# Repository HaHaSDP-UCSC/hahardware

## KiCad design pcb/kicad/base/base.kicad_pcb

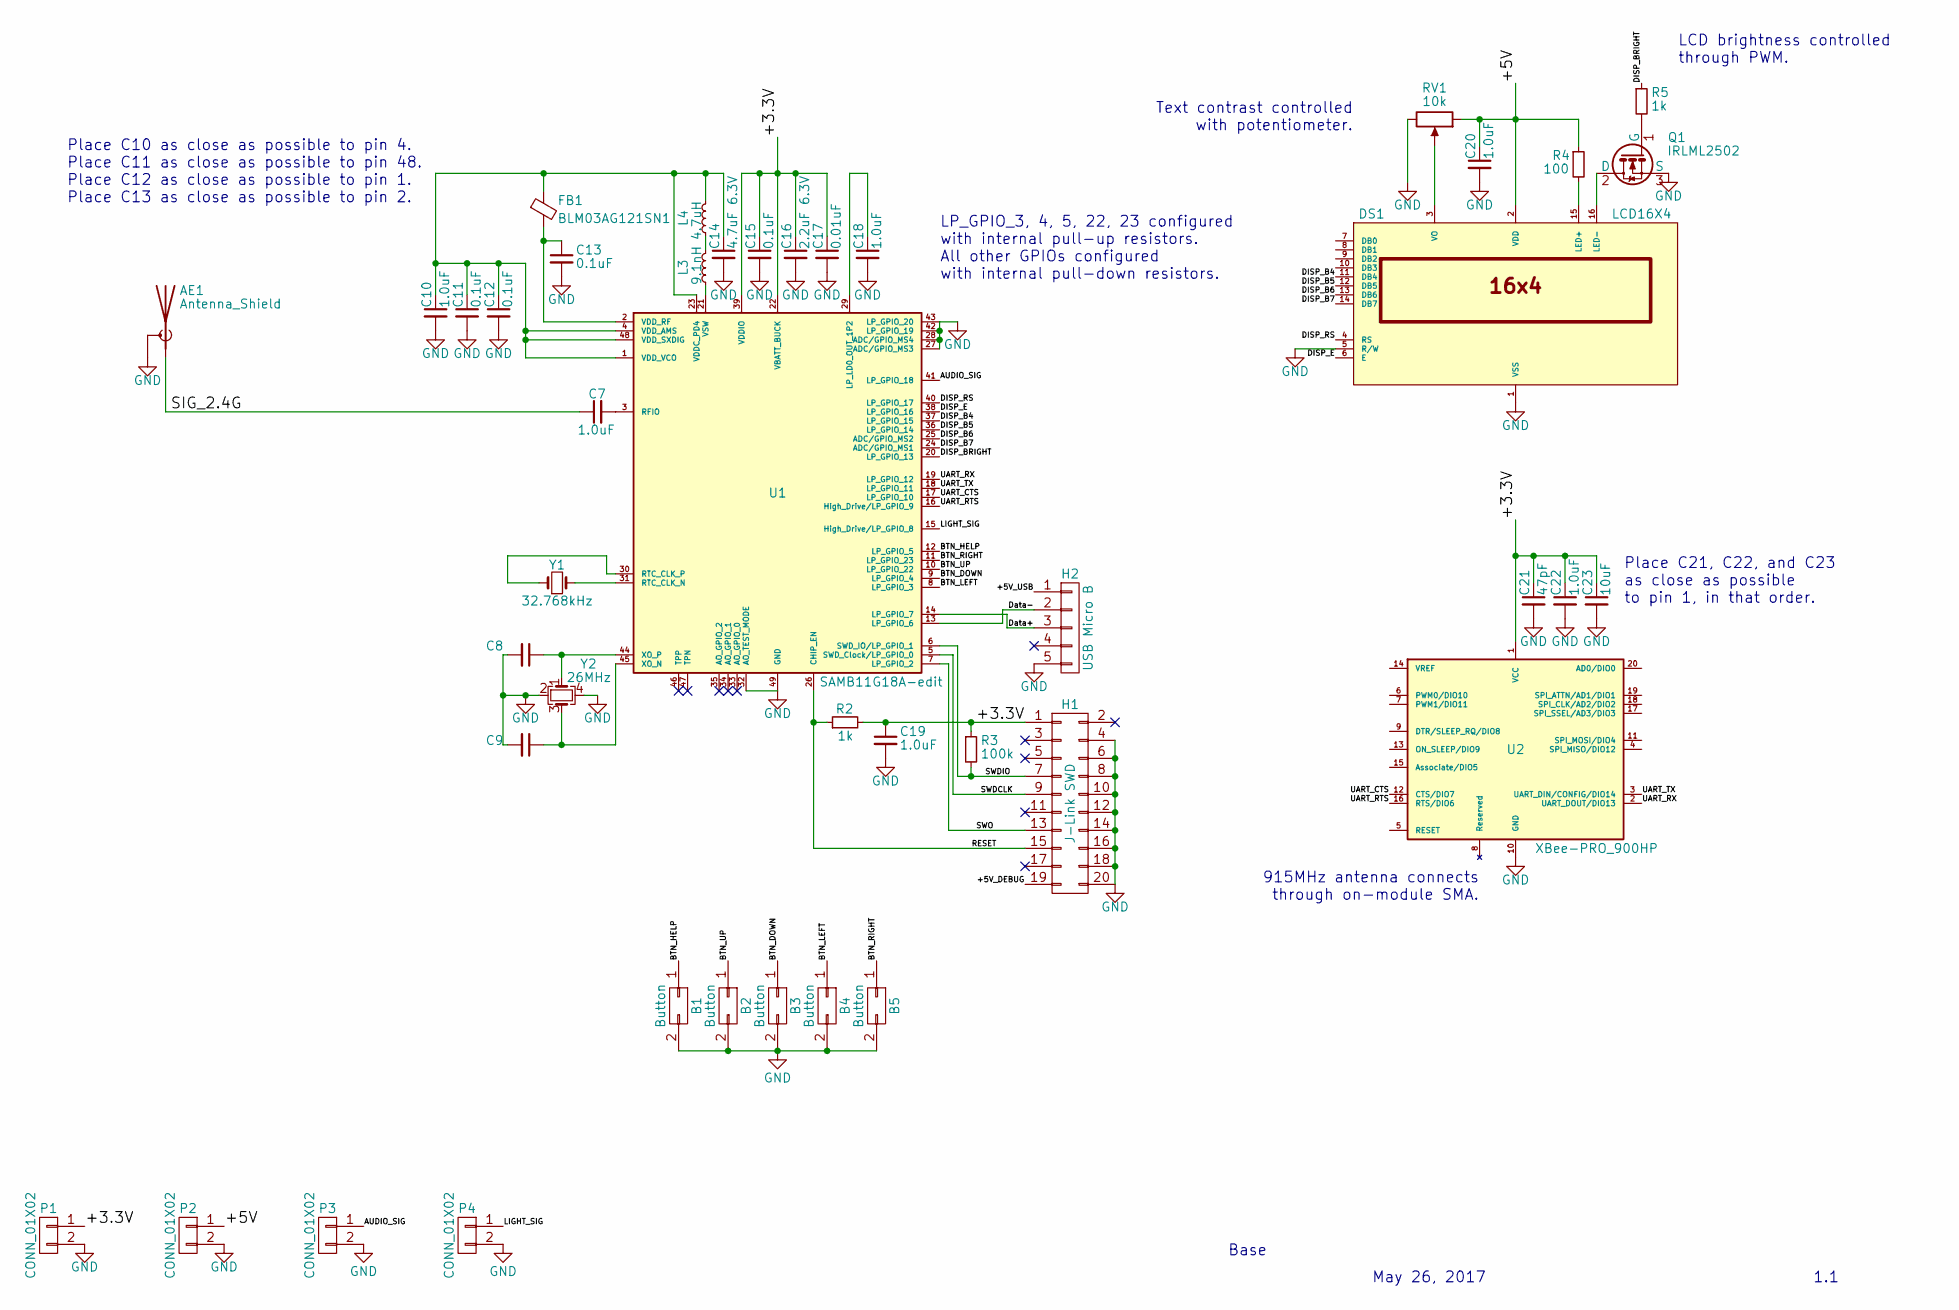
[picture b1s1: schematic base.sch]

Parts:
AE1: Antenna_Shield; Patch_Antenna_2.4GHz
B1, B2, B3, B4, B5: Button; E-Switch_KS01Q01
C7, C10, C18, C19, C20, C22: 1.0uF; C_0402
C8, C9: C_Small; C_0402
C11, C12, C13, C15: 0.1uF; C_0402
C14: 4.7uF 6.3V; C_0402
C16: 2.2uF 6.3V; C_0402
C17: 0.01uF; C_0402
C21: 47pF; C_0402
C23: 10uF; C_0402
DS1: LCD16X4; CFAH1604A
FB1: BLM03AG121SN1; C_0603_HandSoldering
H1: J-Link SWD; Socket_Strip_Straight_2x10_Pitch2.54mm_Drill0.889mm
H2: USB Micro B; USB_Micro-B_10118194-000XLF
L3: 9.1nH; C_0402
L4: 4.7uH; C_0805_HandSoldering
P1, P2, P3, P4: CONN_01X02; OSTTEXX0164_2pin_3.5mm
Q1: IRLML2502; SOT-23
R2, R5: 1k; C_0402
R3: 100k; C_0402
R4: 100; C_0402
RV1: 10k; Potentiometer_Trimmer_Bourns_3309W
U1: SAMB11G18A-edit; QFN-48-1EP_6x6mm_Pitch0.4mm
U2: XBee-PRO_900HP; Digi_XBee-PRO_TH
Y1: 32.768kHz; Crystal_SMD_3215-2pin_3.2x1.5mm
Y2: 26MHz; Crystal_SMD_3225-4pin_3.2x2.5mm

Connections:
/+3.3V: C15.1, C16.1, C17.1, C19.1, C21.1, C22.1, C23.1, H1.1, P1.1, R2.2, R3.1, U1.22 (VBATT_BUCK), U1.39 (VDDIO), U2.1 (VCC)
/+5V: C20.1, DS1.2 (VDD), P2.1, R4.1, RV1.1
/+5V_DEBUG: H1.19
/+5V_USB: H2.1
/AUDIO_SIG: P3.1, U1.41 (LP_GPIO_18)
/BTN_DOWN: B3.1, U1.9 (LP_GPIO_4)
/BTN_HELP: B1.1, U1.12 (LP_GPIO_5)
/BTN_LEFT: B4.1, U1.8 (LP_GPIO_3)
/BTN_RIGHT: B5.1, U1.11 (LP_GPIO_23)
/BTN_UP: B2.1, U1.10 (LP_GPIO_22)
/DISP_B4: DS1.11 (DB4), U1.37 (LP_GPIO_15)
/DISP_B5: DS1.12 (DB5), U1.36 (LP_GPIO_14)
/DISP_B6: DS1.13 (DB6), U1.25 (ADC/GPIO_MS2)
/DISP_B7: DS1.14 (DB7), U1.24 (ADC/GPIO_MS1)
/DISP_BRIGHT: R5.1, U1.20 (LP_GPIO_13)
/DISP_E: DS1.6 (E), U1.38 (LP_GPIO_16)
/DISP_RS: DS1.4 (RS), U1.40 (LP_GPIO_17)
/Data+: H2.3, U1.14 (LP_GPIO_7)
/Data-: H2.2, U1.13 (LP_GPIO_6)
/LIGHT_SIG: P4.1, U1.15 (High_Drive/LP_GPIO_8)
/RESET: H1.15, R2.1, U1.26 (CHIP_EN)
/SIG_2.4G: AE1.1 (A), C7.1
/SWDCLK: H1.9, U1.5 (SWD_Clock/LP_GPIO_0)
/SWDIO: H1.7, R3.2, U1.6 (SWD_IO/LP_GPIO_1)
/SWO: H1.13, U1.7 (LP_GPIO_2)
/UART_CTS: U1.17 (LP_GPIO_10), U2.12 (CTS/DIO7)
/UART_RTS: U1.16 (High_Drive/LP_GPIO_9), U2.16 (RTS/DIO6)
/UART_RX: U1.19 (LP_GPIO_12), U2.2 (UART_DOUT/DIO13)
/UART_TX: U1.18 (LP_GPIO_11), U2.3 (UART_DIN/CONFIG/DIO14)
GND: AE1.2 (Shield), B1.2, B2.2, B3.2, B4.2, B5.2, C8.2, C9.2, C10.2, C11.2, C12.2, C13.2, C14.2, C15.2, C16.2, C17.2, C18.2, C19.2, C20.2, C21.2, C22.2, C23.2, DS1.1 (VSS), DS1.5 (R/W), H1.4, H1.6, H1.8, H1.10, H1.12, H1.14, H1.16, H1.18, H1.20, H2.5, P1.2, P2.2, P3.2, P4.2, Q1.3 (S), RV1.3, U1.27 (ADC/GPIO_MS3), U1.28 (ADC/GPIO_MS4), U1.32 (AO_TEST_MODE), U1.42 (LP_GPIO_19), U1.43 (LP_GPIO_20), U1.49 (GND), U2.10 (GND), Y2.2, Y2.4
unnamed: C7.2, U1.3 (RFIO)
unnamed: C8.1, U1.44 (XO_P), Y2.1
unnamed: C9.1, U1.45 (XO_N), Y2.3
unnamed: C10.1, C11.1, C12.1, C14.1, FB1.1, L4.2, U1.1 (VDD_VCO), U1.4 (VDD_AMS), U1.23 (VDDC_PD4), U1.48 (VDD_SXDIG)
unnamed: C13.1, FB1.2, U1.2 (VDD_RF)
unnamed: C18.1, U1.29 (LP_LD0_OUT_1P2)
unnamed: DS1.3 (VO), RV1.2
unnamed: DS1.15 (LED+), R4.2
unnamed: DS1.16 (LED-), Q1.2 (D)
unnamed: L3.1, U1.21 (VSW)
unnamed: L3.2, L4.1
unnamed: Q1.1 (G), R5.2
unnamed: U1.30 (RTC_CLK_P), Y1.1
unnamed: U1.31 (RTC_CLK_N), Y1.2

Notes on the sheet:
Base
Place C10 as close as possible to pin 4. Place C11 as close as possible to pin 48. Place C12 as close as possible to pin 1. Place C13 as close as possible to pin 2.
LP_GPIO_3, 4, 5, 22, 23 configured with internal pull-up resistors. All other GPIOs configured with internal pull-down resistors.
Place C21, C22, and C23 as close as possible to pin 1, in that order.
915MHz antenna connects through on-module SMA.
May 26, 2017
1.1
Text contrast controlled with potentiometer.
LCD brightness controlled through PWM.

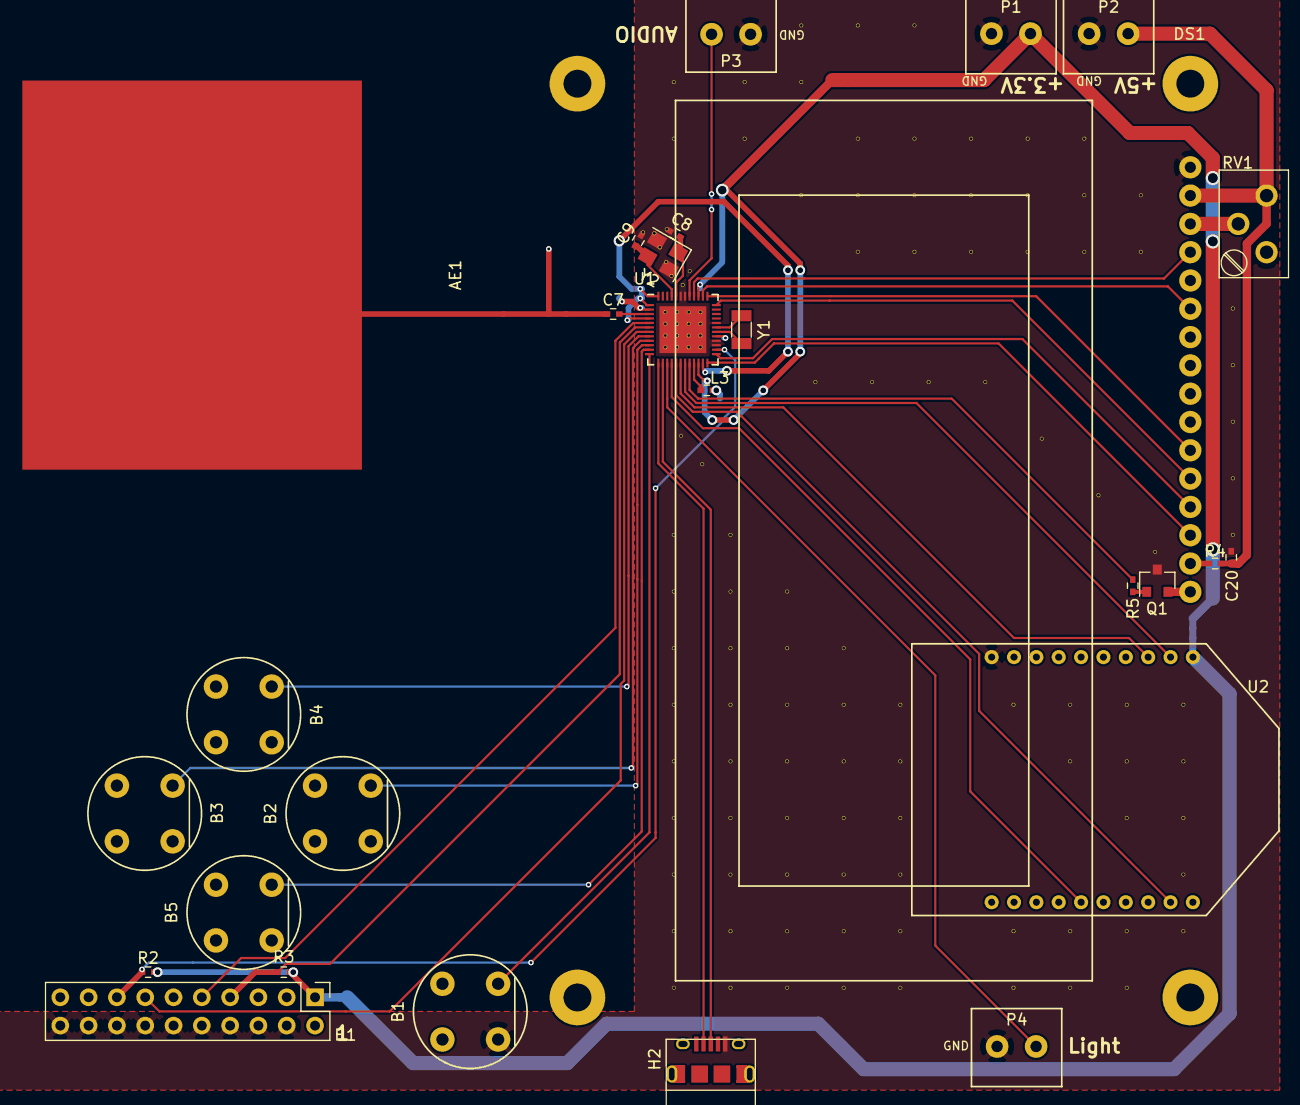
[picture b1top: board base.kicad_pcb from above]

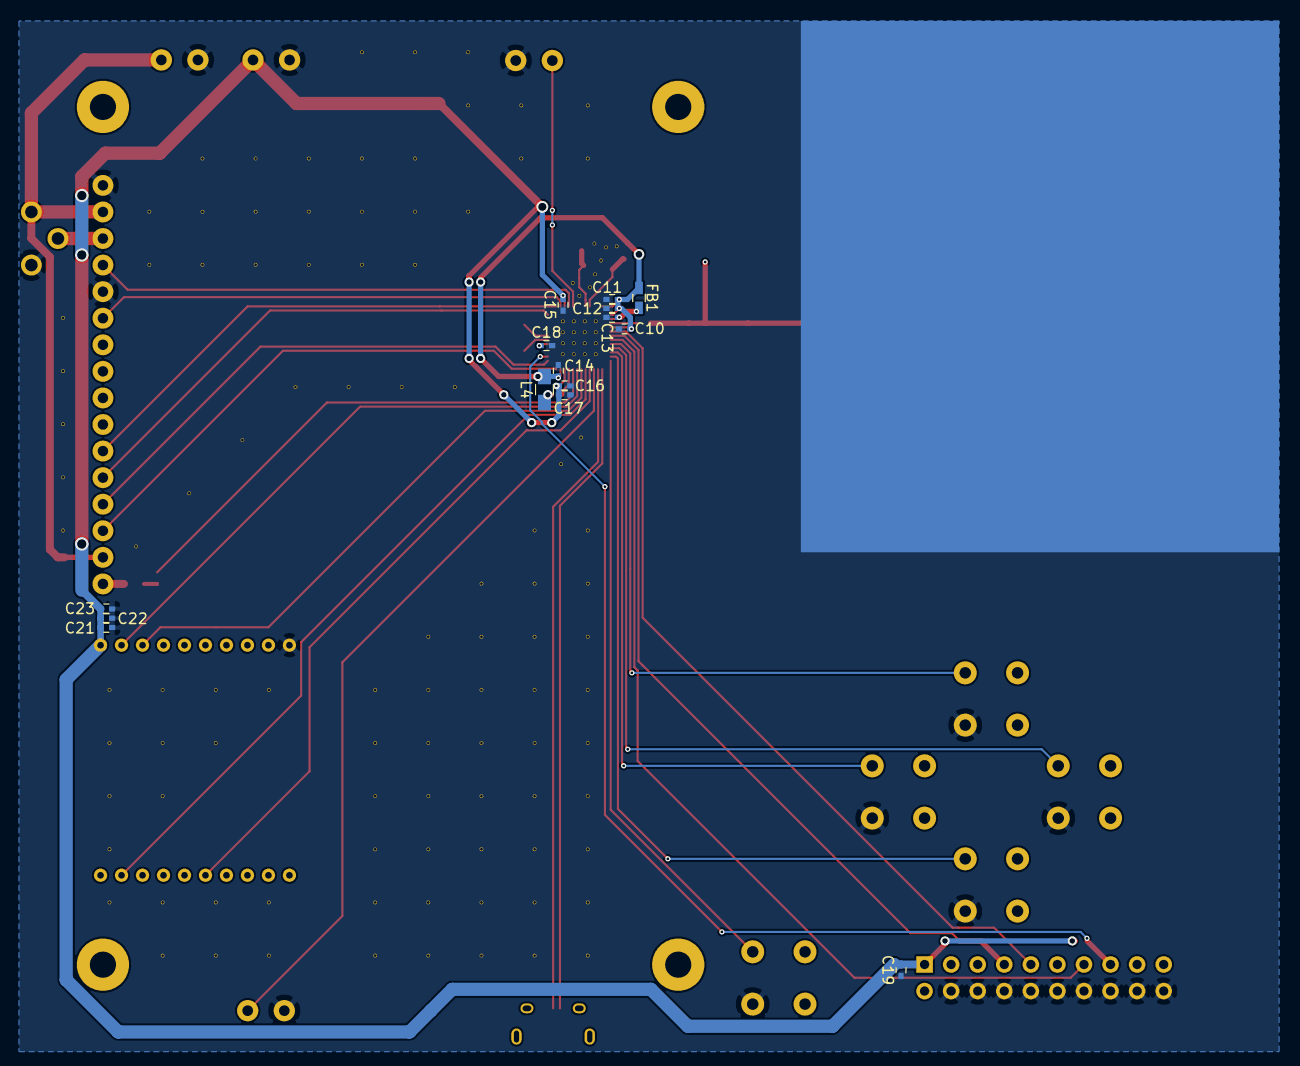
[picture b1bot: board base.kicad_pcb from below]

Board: 2 copper layers, 43 parts (15 on the bottom side), 42 nets.

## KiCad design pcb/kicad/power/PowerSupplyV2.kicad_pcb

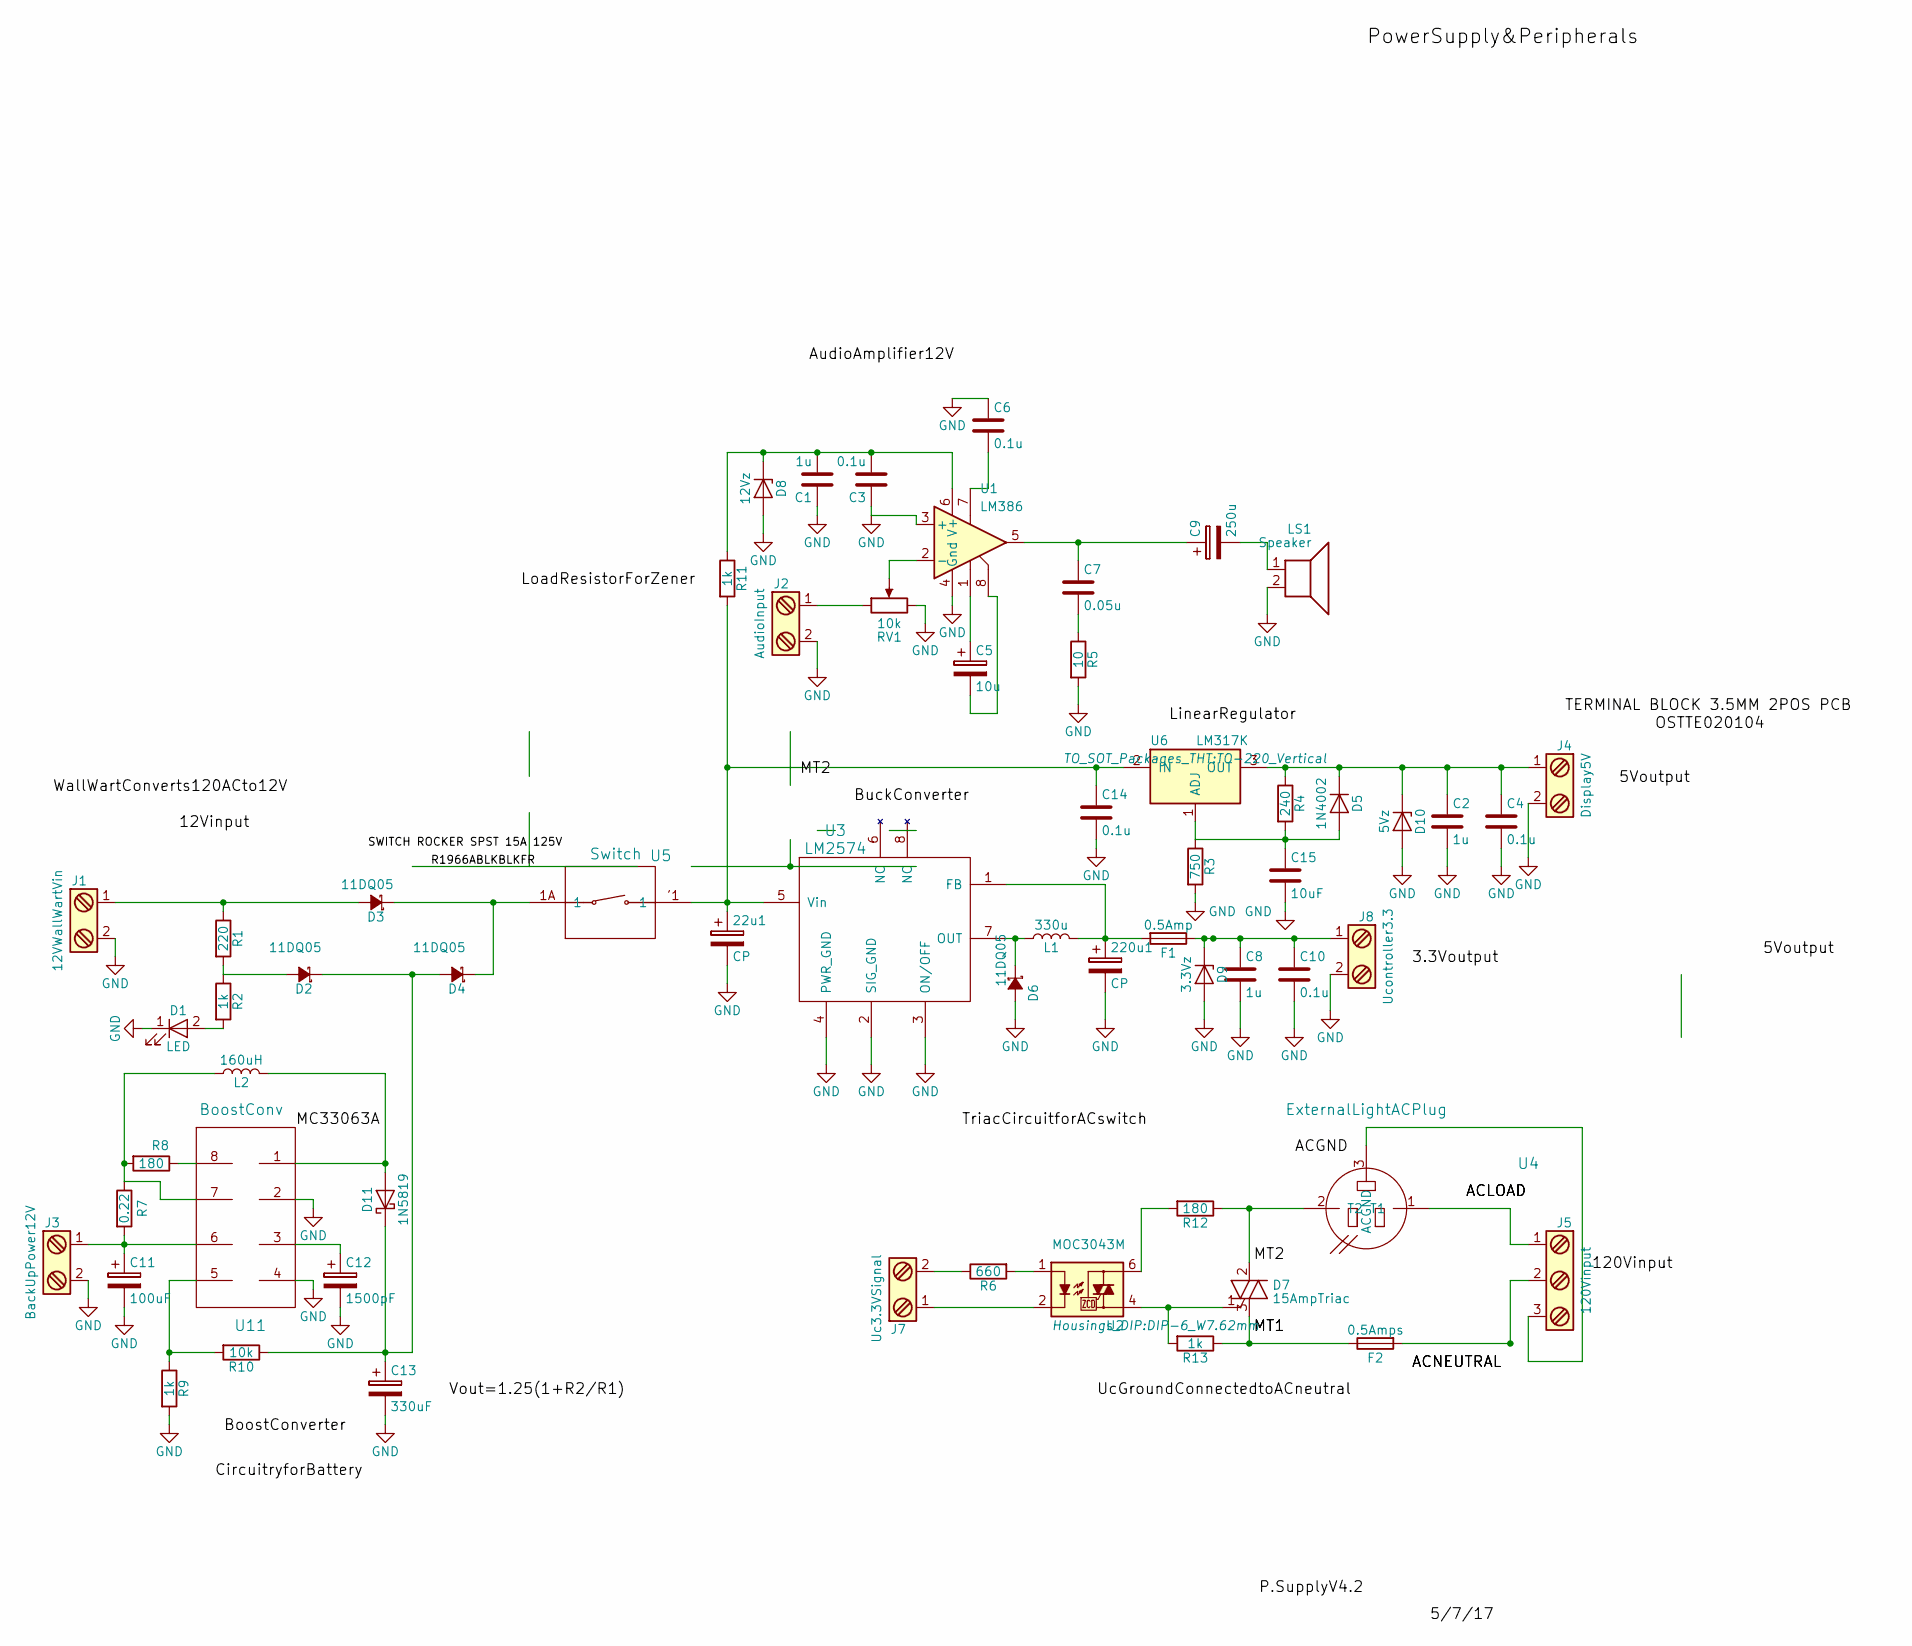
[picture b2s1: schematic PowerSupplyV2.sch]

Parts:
22u1, 220u1: CP; CP_Radial_D6.3mm_P2.50mm
C1, C2, C8: 1u; R_Axial_DIN0204_L3.6mm_D1.6mm_P7.62mm_Horizontal
C3, C4, C6, C10, C14: 0.1u; R_Axial_DIN0204_L3.6mm_D1.6mm_P7.62mm_Horizontal
C5: 10u; CP_Radial_D6.3mm_P2.50mm
C7: 0.05u; C_0805_HandSoldering
C9: 250u; CP_Radial_D6.3mm_P2.50mm
C11: 100uF; CP_Radial_D6.3mm_P2.50mm
C12: 1500pF; CP_Radial_D6.3mm_P2.50mm
C13: 330uF; CP_Radial_D6.3mm_P2.50mm
C15: 10uF; R_Axial_DIN0204_L3.6mm_D1.6mm_P7.62mm_Horizontal
D1: LED; LED_D5.0mm_Horizontal_O1.27mm_Z3.0mm
D2, D3, D4, D6: 11DQ05; D_DO-15_P5.08mm_Vertical_KathodeUp
D5: 1N4002; D_DO-15_P5.08mm_Vertical_KathodeUp
D7: 15AmpTriac; TO-220_Vertical
D8: 12Vz; D_SOD-323_HandSoldering
D9: 3.3Vz; D_SOD-323_HandSoldering
D10: 5Vz; D_SOT-23_ANK
D11: 1N5819; D_DO-15_P5.08mm_Vertical_KathodeUp
F1: 0.5Amp; FuseTH500mA
F2: 0.5Amps; FuseTH500mA
J1: 12VWallWartVin; BARREL_JACK
J2: AudioInput; BlockTerminal3.5mm
J3: BackUpPower12V; NIMH4.8V
J4: Display5V; BlockTerminal3.5mm
J5: 120Vinput; 703w0053
J7: Uc3.3VSignal; BlockTerminal3.5mm
J8: Ucontroller3.3; BlockTerminal3.5mm
L1: 330u; Choke_SMD_12x12mm_h4.5mm
L2: 160uH; Choke_SMD_12x12mm_h4.5mm
LS1: Speaker; BlockTerminal3.5mm
R1: 220; R_Axial_DIN0309_L9.0mm_D3.2mm_P2.54mm_Vertical
R2, R9, R11, R13: 1k; R_Axial_DIN0309_L9.0mm_D3.2mm_P2.54mm_Vertical
R3: 750; R_Axial_DIN0309_L9.0mm_D3.2mm_P2.54mm_Vertical
R4: 240; R_Axial_DIN0309_L9.0mm_D3.2mm_P2.54mm_Vertical
R5: 10; R_0805_HandSoldering
R6: 660; R_Axial_DIN0309_L9.0mm_D3.2mm_P2.54mm_Vertical
R7: 0.22; R_Axial_DIN0309_L9.0mm_D3.2mm_P2.54mm_Vertical
R8, R12: 180; R_Axial_DIN0309_L9.0mm_D3.2mm_P2.54mm_Vertical
R10: 10k; R_Axial_DIN0309_L9.0mm_D3.2mm_P2.54mm_Vertical
RV1: 10k; Potentiometer_Alps_RK09K_Vertical
U1: LM386; DIP-8_W7.62mm
U2: MOC3043M; DIP-6_W7.62mm
U3: LM2574; PDIP-8
U4: ExternalLightACPlug; 739W-X203
U5: Switch
U6: LM317K; TO-220_Vertical
U11: BoostConv; DIP-8_W7.62mm

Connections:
GND: 22u1.2, 220u1.2, C1.1, C2.2, C3.1, C4.2, C6.1, C8.2, C10.2, C11.2, C12.2, C13.2, C14.2, C15.2, D1.1 (K), D6.2 (A), D8.2 (A), D9.2 (A), D10.2 (A), J1.2, J2.2, J3.2, J4.2, J8.2, LS1.2, R3.2, R5.2, R9.2, RV1.3, U1.3 (+), U1.4 (Gnd), U3.2 (SIG_GND), U3.3 (ON/OFF), U3.4 (PWR_GND), U11.2, U11.4
unnamed: 22u1.1, C14.1, R11.2, U3.5 (Vin), U5.'1, U6.2 (IN)
unnamed: 220u1.1, F1.2, L1.2, U3.1 (FB)
unnamed: C1.2, C3.2, D8.1 (K), R11.1, U1.6 (V+)
unnamed: C2.1, C4.1, D5.1 (K), D10.1 (K), J4.1, R4.1, U6.3 (OUT)
unnamed: C5.1, U1.1
unnamed: C5.2, U1.8
unnamed: C6.2, U1.7
unnamed: C7.1, C9.1, U1.5
unnamed: C7.2, R5.1
unnamed: C9.2, LS1.1
unnamed: C8.1, C10.1, D9.1 (K), F1.1, J8.1
unnamed: C11.1, J3.1, R7.2, U11.6
unnamed: C12.1, U11.3
unnamed: C13.1, D2.1 (K), D4.2 (A), D11.1 (K), R10.1
unnamed: C15.1, D5.2 (A), R3.1, R4.2, U6.1 (ADJ)
unnamed: D1.2 (A), R2.2
unnamed: D2.2 (A), R1.2, R2.1
unnamed: D3.1 (K), D4.1 (K), U5.1A
unnamed: D3.2 (A), J1.1, R1.1
unnamed: D6.1 (K), L1.1, U3.7 (OUT)
unnamed: D7.1 (G), R13.2, U2.4
unnamed: D7.2 (A1), R12.1, U4.2 (T2)
unnamed: D7.3 (A2), F2.1, R13.1
unnamed: D11.2 (A), L2.2, U11.1
unnamed: F2.2, J5.2
unnamed: J2.1, RV1.1
unnamed: J5.1, U4.1 (T1)
unnamed: J5.3, U4.3 (ACGND)
unnamed: J7.1, U2.2
unnamed: J7.2, R6.1
unnamed: L2.1, R7.1, R8.2, U11.7
unnamed: R6.2, U2.1
unnamed: R8.1, U11.8
unnamed: R9.1, R10.2, U11.5
unnamed: R12.2, U2.6
unnamed: RV1.2, U1.2 (-)

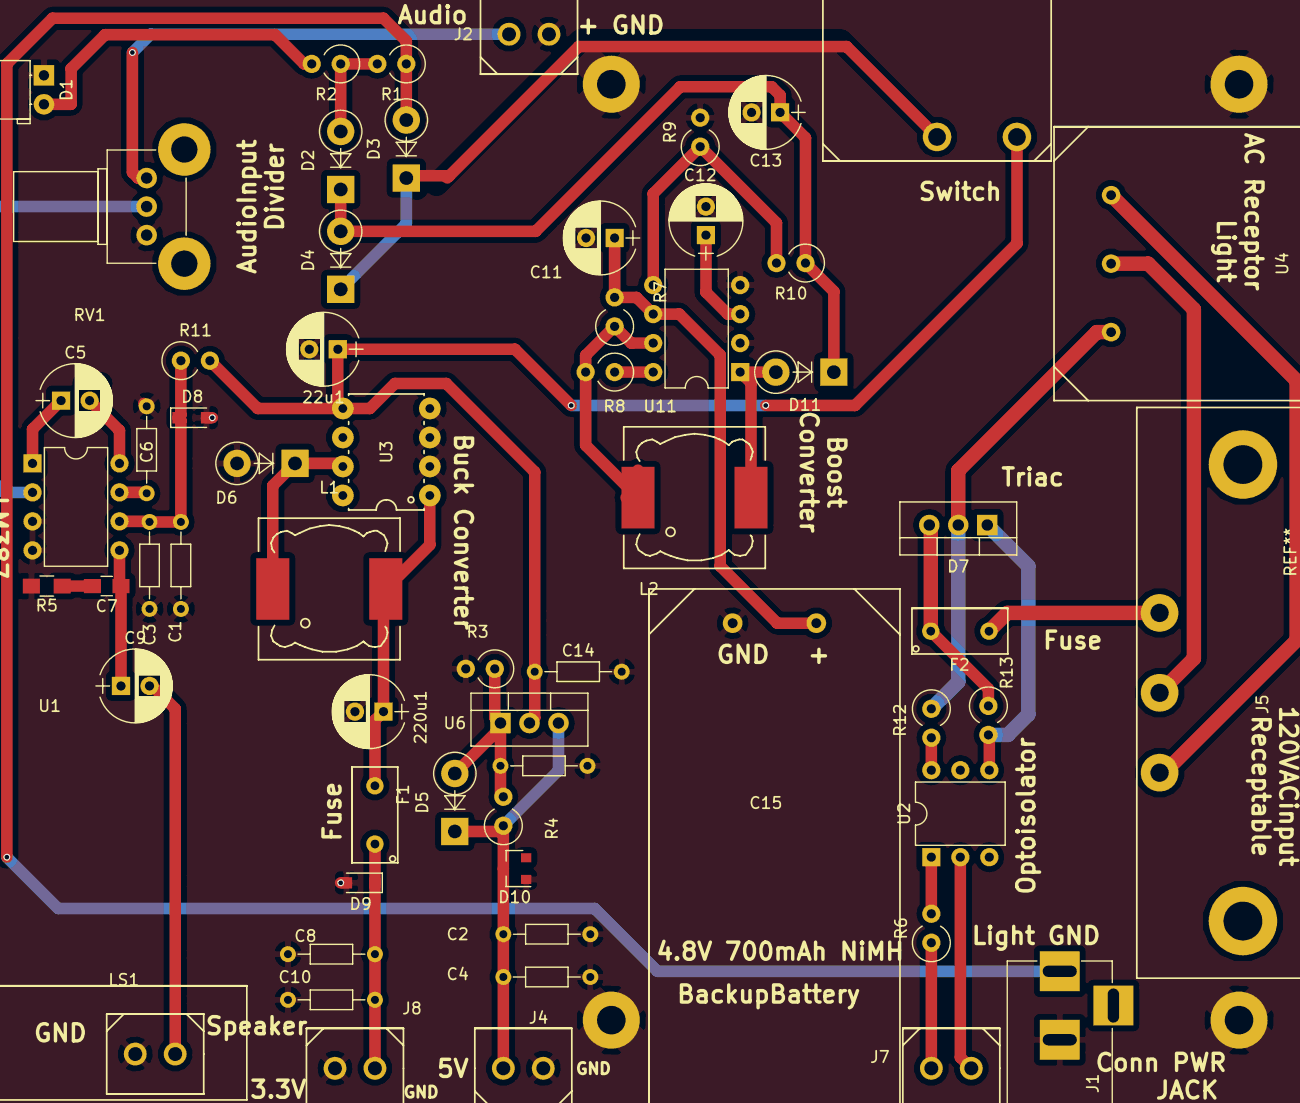
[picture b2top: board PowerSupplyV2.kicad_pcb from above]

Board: 2 copper layers, 61 parts (0 on the bottom side), 37 nets.

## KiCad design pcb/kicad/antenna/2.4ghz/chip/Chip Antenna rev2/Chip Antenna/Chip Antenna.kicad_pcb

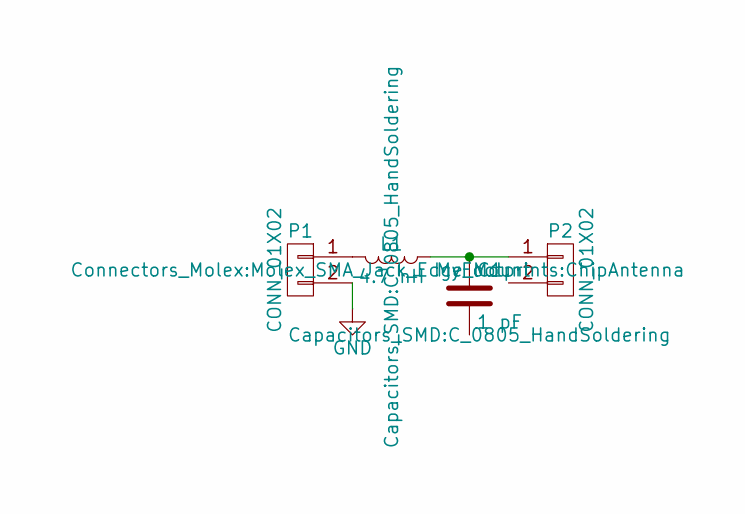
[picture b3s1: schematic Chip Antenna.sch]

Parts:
C1: 1 pF; C_0805_HandSoldering
L1: 4.7 nH; C_0805_HandSoldering
P1: CONN_01X02; Molex_SMA_Jack_Edge_Mount
P2: CONN_01X02; ChipAntenna

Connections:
GND: P1.2
unnamed: C1.1, L1.1, P2.1
unnamed: L1.2, P1.1

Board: 2 copper layers, 4 parts (0 on the bottom side), 2 nets, no tracks yet.

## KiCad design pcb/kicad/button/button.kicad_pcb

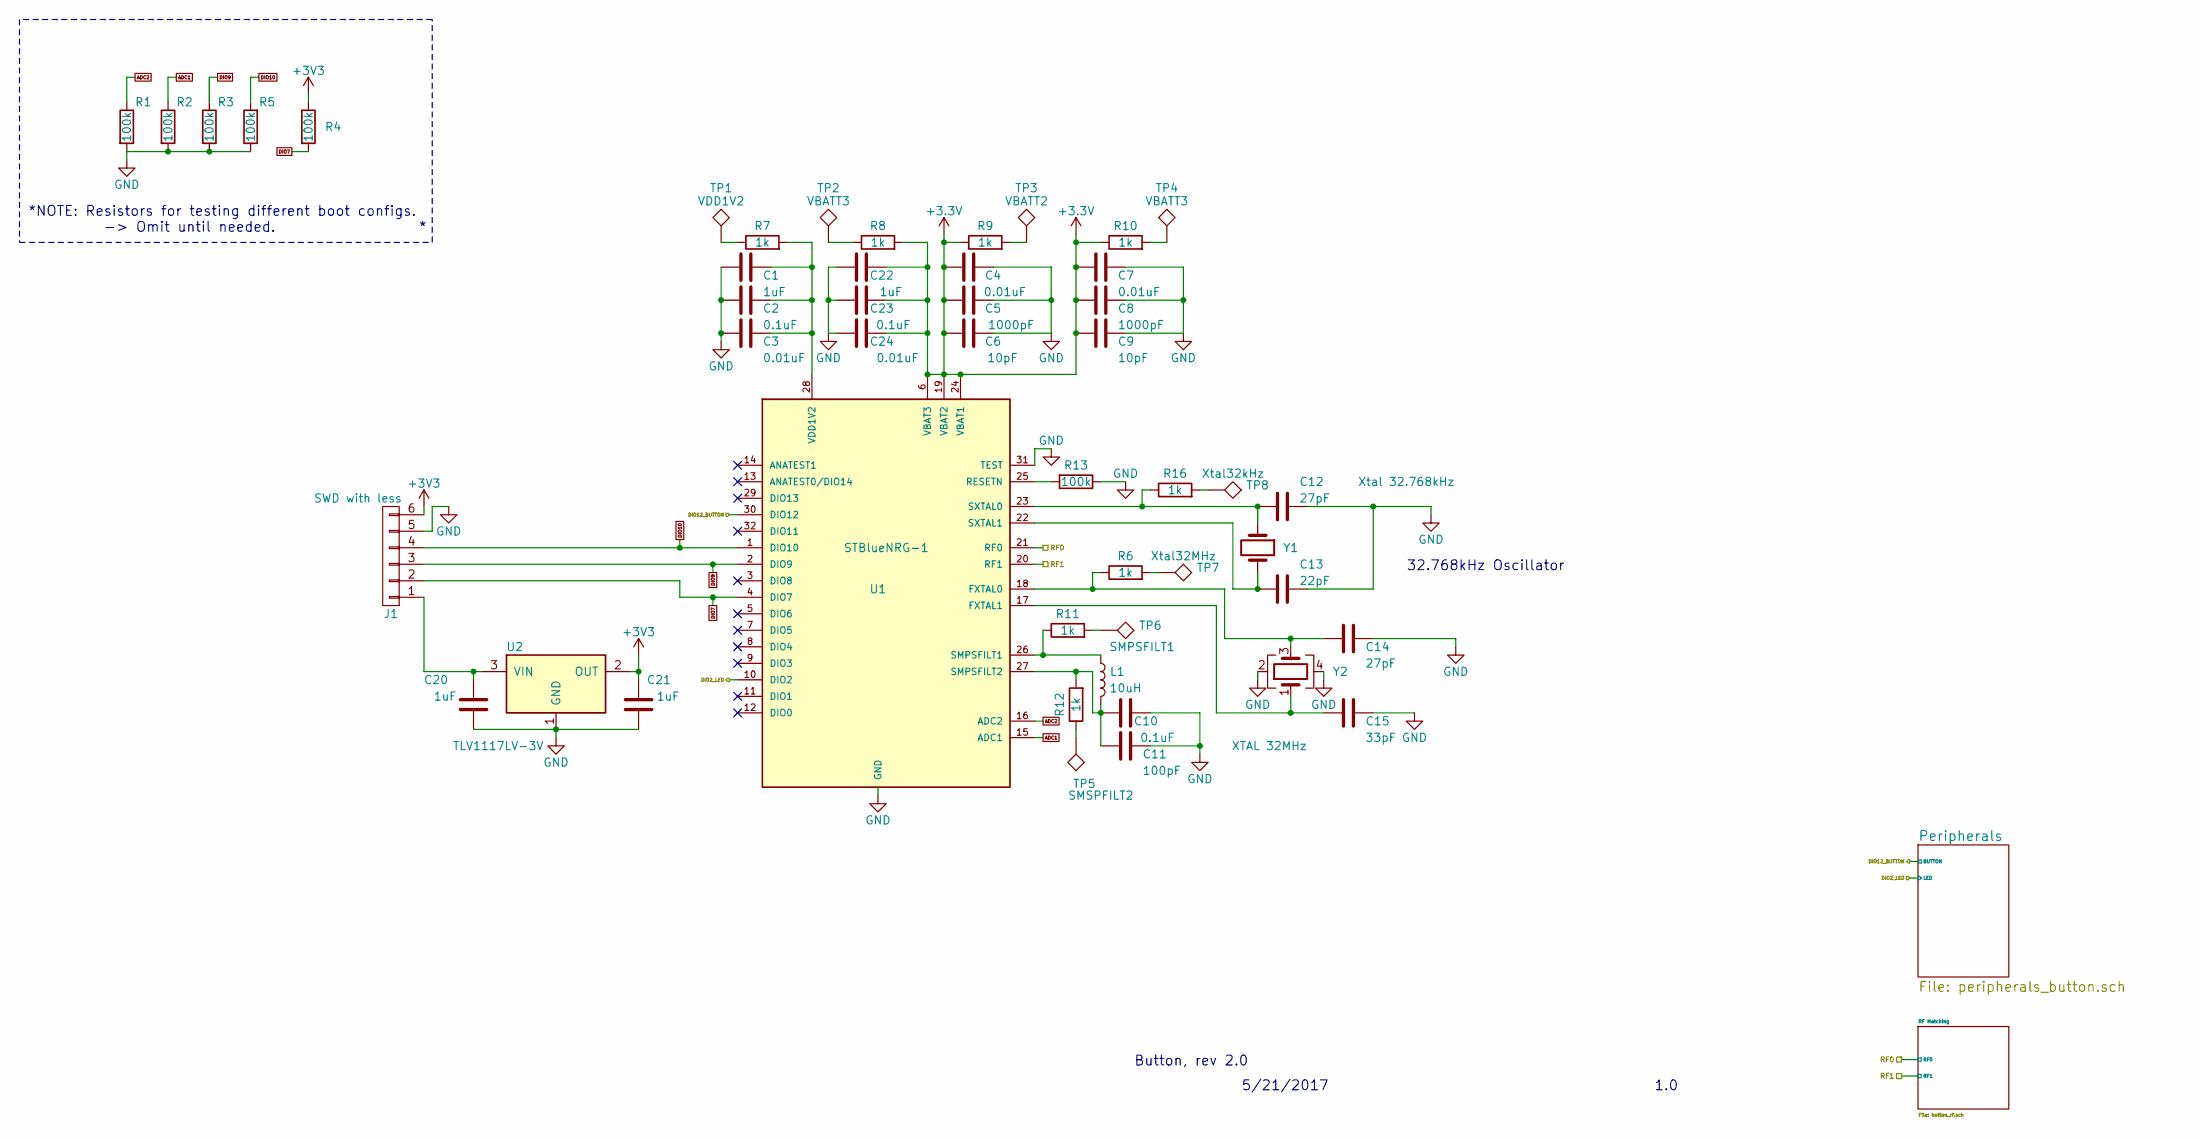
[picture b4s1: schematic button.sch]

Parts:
C1, C22: 1uF; C_0805
C2, C23: 0.1uF; C_0603
C3, C24: 0.01uF; C_0402
C4, C7: 0.01uF; C_0805
C5, C8: 1000pF; C_0603
C6, C9: 10pF; C_0402
C10: 0.1uF; C_0402
C11: 100pF; C_0402
C12, C14: 27pF; C_0402
C13: 22pF; C_0402
C15: 33pF; C_0402
C20, C21: 1uF; C_0402
J1: SWD with less; Pin_Header_Straight_1x06_Pitch2.54mm
L1: 10uH; Neosid_Inductor_SM-NE29_SMD1008
R1, R2, R3, R4, R5, R13: 100k; R_0402
R6, R9, R11, R12, R16: 1k; R_0402
R7, R8, R10: 1k; R_0603
TP1: VDD1V2; Measurement_Point_Round-SMD-tiniest
TP2, TP4: VBATT3; Measurement_Point_Round-SMD-tiniest
TP3: VBATT2; Measurement_Point_Round-SMD-tiniest
TP5: SMSPFILT2; Measurement_Point_Round-SMD-tiniest
TP6: SMPSFILT1; Measurement_Point_Round-SMD-tiniest
TP7: Xtal32MHz; Measurement_Point_Round-SMD-tiniest
TP8: Xtal32kHz; Measurement_Point_Round-SMD-tiniest
U1: STBlueNRG-1; STBNRG1
U2: TLV1117LV-3V; SOT-223
Y1: Xtal 32.768kHz; Crystal_SMD_3215-2pin_3.2x1.5mm
Y2: XTAL 32MHz; Crystal_SMD_2520-4pin_2.5x2.0mm

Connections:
/DIO2_LED: U1.10 (DIO2); also elsewhere on the board
/DIO12_BUTTON: U1.30 (DIO12); also elsewhere on the board
/RF0: U1.21 (RF0); also elsewhere on the board
/RF1: U1.20 (RF1); also elsewhere on the board
ADC1: R2.1, U1.15 (ADC1)
ADC2: R1.1, U1.16 (ADC2)
DIO7: J1.2, R4.2, U1.4 (DIO7)
DIO9: J1.3, R3.1, U1.2 (DIO9)
DIO10: J1.4, R5.2, U1.1 (DIO10)
GND: C1.2, C2.2, C3.2, C4.2, C5.2, C6.2, C7.1, C8.1, C9.1, C10.2, C11.1, C12.1, C13.1, C14.1, C15.1, C20.1, C21.1, C22.1, C23.1, C24.1, J1.5, R1.2, R2.2, R3.2, R5.1, R13.1, U1.31 (TEST), U1.33 (GND), U2.1 (GND), Y2.2, Y2.4; also elsewhere on the board
unnamed: C1.1, C2.1, C3.1, R7.2, U1.28 (VDD1V2)
unnamed: C10.1, C11.2, L1.2, R12.2, U1.27 (SMPSFILT2)
unnamed: C12.2, R16.1, U1.23 (SXTAL0), Y1.1
unnamed: C13.2, U1.22 (SXTAL1), Y1.2
unnamed: C14.2, R6.1, U1.18 (FXTAL0), Y2.3
unnamed: C15.2, U1.17 (FXTAL1), Y2.1
unnamed: C20.2, J1.1, U2.3 (VIN)
unnamed: L1.1, R11.1, U1.26 (SMPSFILT1)
unnamed: R6.2, TP7.1
unnamed: R7.1, TP1.1
unnamed: R8.1, TP2.1
unnamed: R9.2, TP3.1
unnamed: R10.2, TP4.1
unnamed: R11.2, TP6.1
unnamed: R12.1, TP5.1
unnamed: R13.2, U1.25 (RESETN)
unnamed: R16.2, TP8.1

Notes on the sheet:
Button, rev 2.0
1.0
5/21/2017
32.768kHz Oscillator
*NOTE: Resistors for testing different boot configs. -> Omit until needed. *

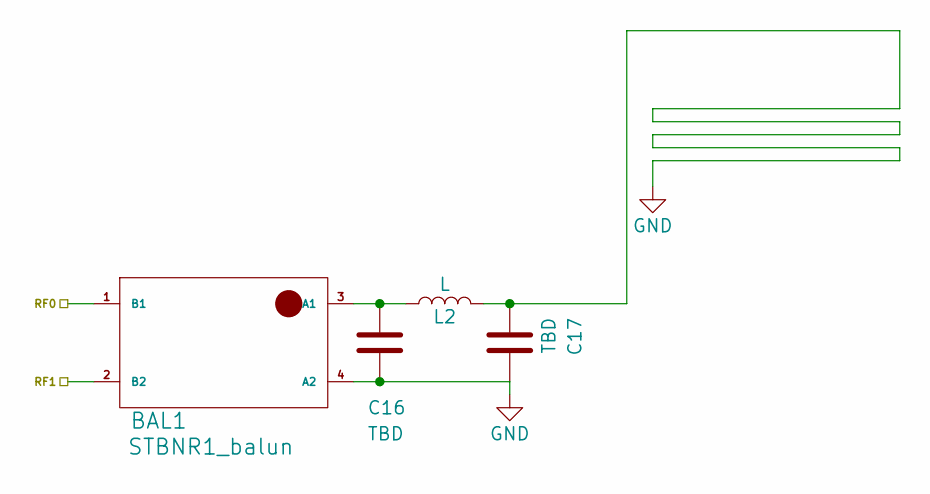
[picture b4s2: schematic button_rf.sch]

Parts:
BAL1: STBNR1_balun; BNRG1_balun
C16, C17: TBD; C_0402
L2: L; C_0603_HandSoldering

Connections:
/RF0: BAL1.1 (B1); also elsewhere on the board
/RF1: BAL1.2 (B2); also elsewhere on the board
GND: BAL1.4 (A2), C16.2, C17.1, C17.2, L2.2; also elsewhere on the board
unnamed: BAL1.3 (A1), C16.1, L2.1

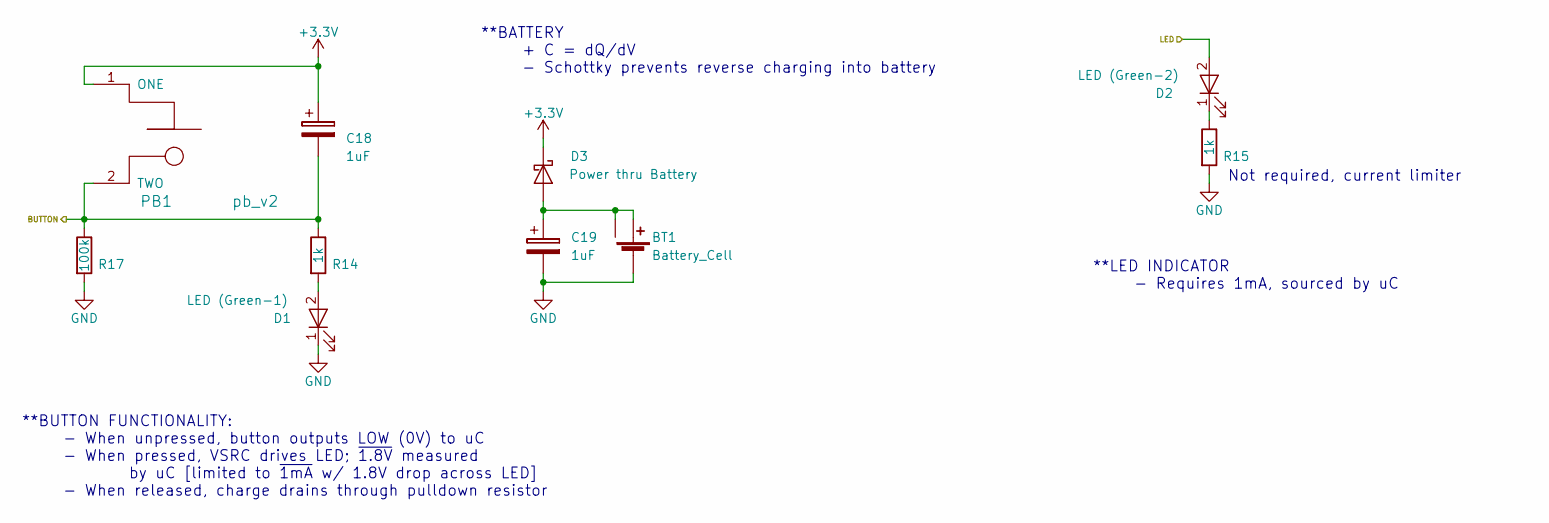
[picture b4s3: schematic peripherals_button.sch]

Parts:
BT1: Battery_Cell; CoinCell_holder_1060x630
C18, C19: 1uF; C_0603_HandSoldering
D1: LED (Green-1); LED_0402
D2: LED (Green-2); LED_0402
D3: Power thru Battery; D_0603
PB1: pb_v2; SW_PUSH-12mm
R14, R15: 1k; R_0402
R17: 100k; R_0402

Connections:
/DIO2_LED: D2.2 (A); also elsewhere on the board
/DIO12_BUTTON: C18.2, PB1.2 (TWO), R14.1, R17.1; also elsewhere on the board
GND: BT1.3 (-), C19.2, D1.1 (K), R15.2, R17.2; also elsewhere on the board
unnamed: BT1.1 (+), BT1.2 (++), C19.1, D3.2 (A)
unnamed: D1.2 (A), R14.2
unnamed: D2.1 (K), R15.1

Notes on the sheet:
**BUTTON FUNCTIONALITY: - When unpressed, button outputs LOW (0V) to uC - When pressed, VSRC drives LED; ~1.8V measured by uC [limited to ~1mA w/ 1.8V drop across LED] - When released, charge drains through pulldown resistor
**BATTERY + C = dQ/dV - Schottky prevents reverse charging into battery
**LED INDICATOR - Requires 1mA, sourced by uC
Not required, current limiter

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
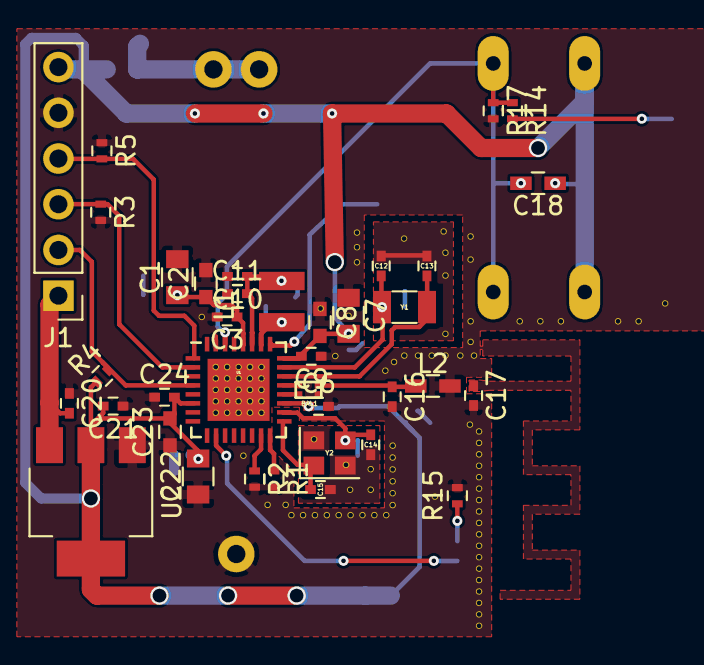
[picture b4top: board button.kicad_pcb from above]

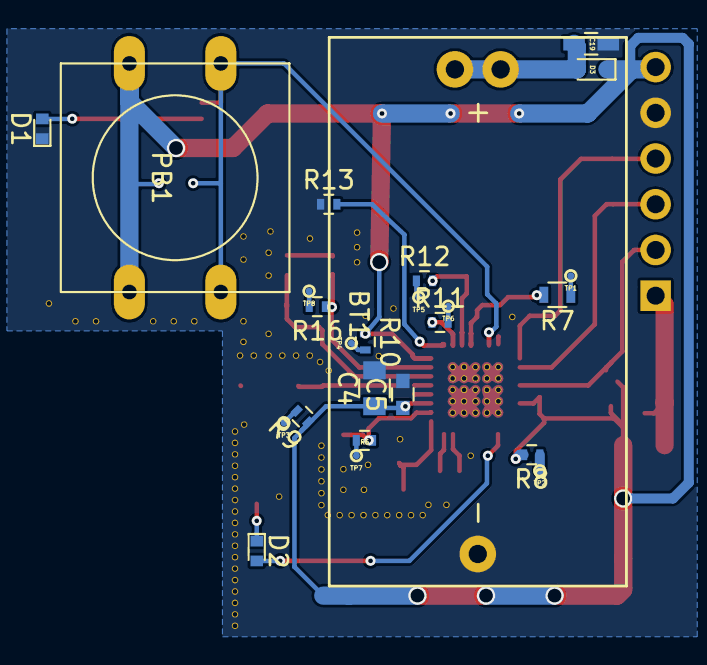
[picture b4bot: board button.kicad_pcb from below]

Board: 2 copper layers, 62 parts (25 on the bottom side), 32 nets.
